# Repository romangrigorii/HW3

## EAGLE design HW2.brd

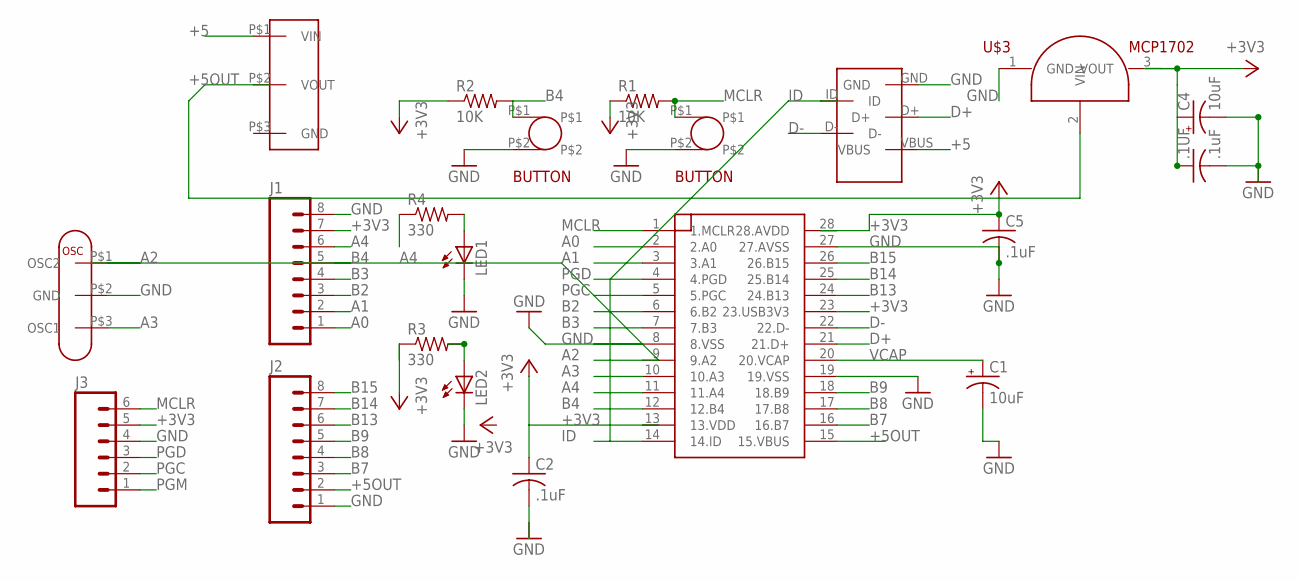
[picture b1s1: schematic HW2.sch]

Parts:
.1UF: .1uF; C025-024X044
C1, C4: 10uF; B45181A
C2, C5: .1uF; C025-024X044
J1, J2: M08; 1X08_ROUND
J3: M06SILK_FEMALE_PTH; 1X06
LED1, LED2: LED3MM
R1, R2: 10K; 0207/10
R3, R4: 330; 0207/10
U$1: PIC32; DIL28-3
U$2: USB-MINI-B; USB-MB-H
U$3: MCP1702; TO92
U$4, U$5: BUTTON
U$6: SWITCH
U$7: OSCILLATOR

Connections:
+3V3: .1UF.1, C2.1, C4.+, C5.1, J1.7, J3.5, R1.1, R2.1, R3.1, U$1.13 (13.VDD), U$1.23 (23.USB3V3), U$1.28 (28.AVDD), U$3.3 (VOUT)
+5: U$2.VBUS, U$6.P$1 (VIN)
+5OUT: J2.2, U$1.15 (15.VBUS), U$3.2 (VIN), U$6.P$2 (VOUT)
A0: J1.1, U$1.2 (2.A0)
A1: J1.2, U$1.3 (3.A1)
A2: U$1.9 (9.A2), U$7.P$1 (OSC2)
A3: U$1.10 (10.A3), U$7.P$3 (OSC1)
A4: J1.6, R4.1, U$1.11 (11.A4)
B2: J1.3, U$1.6 (6.B2)
B3: J1.4, U$1.7 (7.B3)
B4: J1.5, R2.2, U$1.12 (12.B4), U$5.P$1
B7: J2.3, U$1.16 (16.B7)
B8: J2.4, U$1.17 (17.B8)
B9: J2.5, U$1.18 (18.B9)
B13: J2.6, U$1.24 (24.B13)
B14: J2.7, U$1.25 (25.B14)
B15: J2.8, U$1.26 (26.B15)
D+: U$1.21 (21.D+), U$2.D+
D-: U$1.22 (22.D-), U$2.D-
GND: .1UF.2, C1.-, C4.-, C5.2, J1.8, J2.1, J3.4, LED1.K (C), LED2.K (C), U$1.8 (8.VSS), U$1.19 (19.VSS), U$1.27 (27.AVSS), U$2.GND, U$3.1 (GND), U$4.P$2, U$5.P$2, U$7.P$2 (GND)
ID: U$1.14 (14.ID), U$2.ID
MCLR: J3.6, R1.2, U$1.1 (1.MCLR), U$4.P$1
unnamed: LED2.A, R3.2
unnamed: LED1.A, R4.2
PGC: J3.2, U$1.5 (5.PGC)
PGD: J3.3, U$1.4 (4.PGD)
PGM: J3.1
VCAP: C1.+, U$1.20 (20.VCAP)

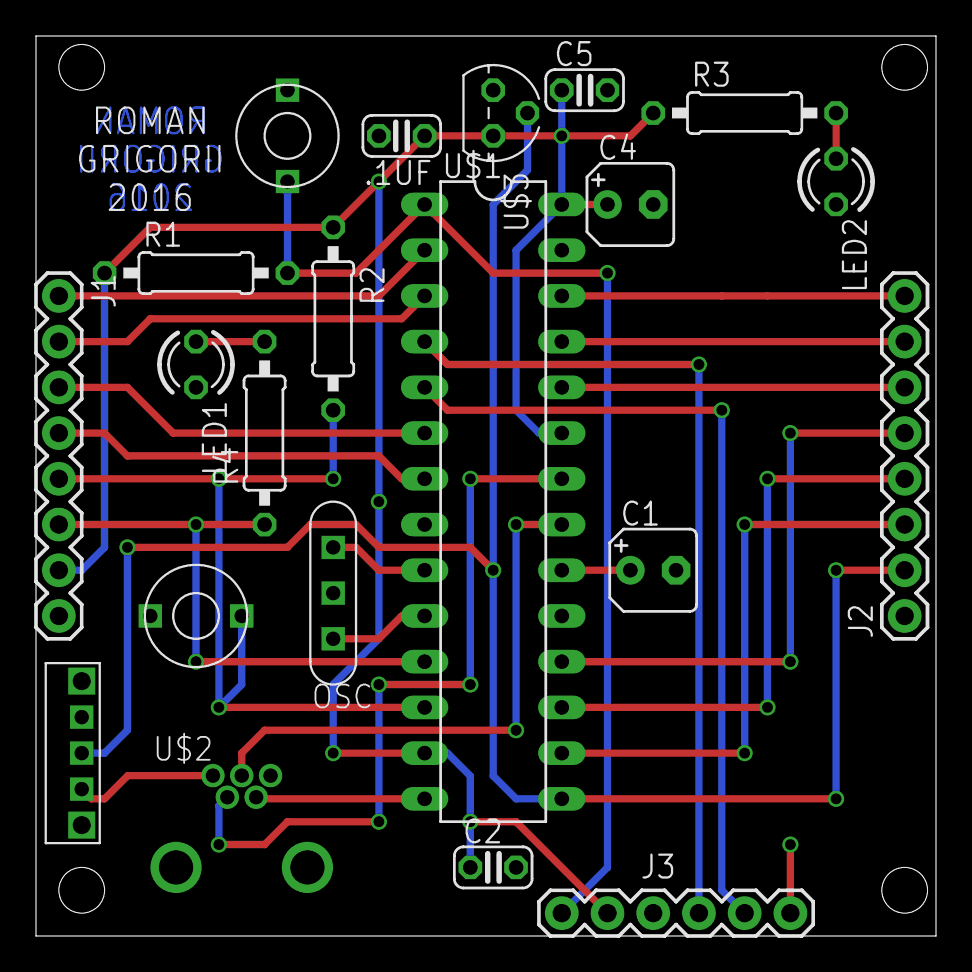
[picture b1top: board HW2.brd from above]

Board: 2 copper layers, 50.0 x 50.0 mm, 21 parts (0 on the bottom side), 27 nets.

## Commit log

2016-04-14 "Ready to be checked before order
    "Ready to be checked before order
